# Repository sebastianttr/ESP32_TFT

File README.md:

# ESP32 2.4 inch TFT display driver
A ESP32 TFT board with USB Type C and additional headers for adding sensors.

For any questions make, sure to contact me. You can also DM me at @wired_less_maker
.

# Parts List

This project requires several components: 

* ESP32 WROOM module
  * Preferably a ESP32U or a ESP32S, because of the ability to add an external antenna for better wireless performance
  
* USB Type C Receptable
  * Make sure you select the correct receptable, this is the footprint

* CH340 USB to TTL Converter IC
* LD1117 3V3 Regulator IC
* [OPTIONAL] RFM95 for LoRaWAN
   * If you decide on using LoRaWAN, make sure to also get a U.FL antenna connector 
* 2 SMD Buttons (6 mm X 3.9 mm)
* Passive components
   * 4x 10kOhm 0805 Resistor
   * 2x 5.1kOhm 0805 Resistor 
   * 2x 12kOhm 0805 Resistor
   * 1x Schottky Diode 1206 (the choice is yours)
   * 2x 100nF 0805 Capacitor
   * 1x 10uF 1206 Capacitor
   * 2x 22pF 0603 Capacitor 
   * 1x 12Mhz SMD Crystal 5.0 mm x 3.2 mm
     
     * You will need this configuration. Make sure to look into the datasheet 

   * 2x SOT-23-3 BJT Tranistor of either types: MMBT1000 or MMBT2222
     * S8050 is also OK
* LED
  * For LED, you can use whatever you like.
  * The LED Pin outputs 3.3V from the ESP32, in case you use a LED with a forward voltage lower than ~ 3.3V, you can calculate and add your own resistor at R10
  
# Before usage
  * Before using the device with the TFT touchscreen, make sure to jump these 2 pins above the touchscreen connector: 

  These pins exist to set the brightness of the backlight. In this case, we connect the LED- pin from the touchscreen with 3.3V.

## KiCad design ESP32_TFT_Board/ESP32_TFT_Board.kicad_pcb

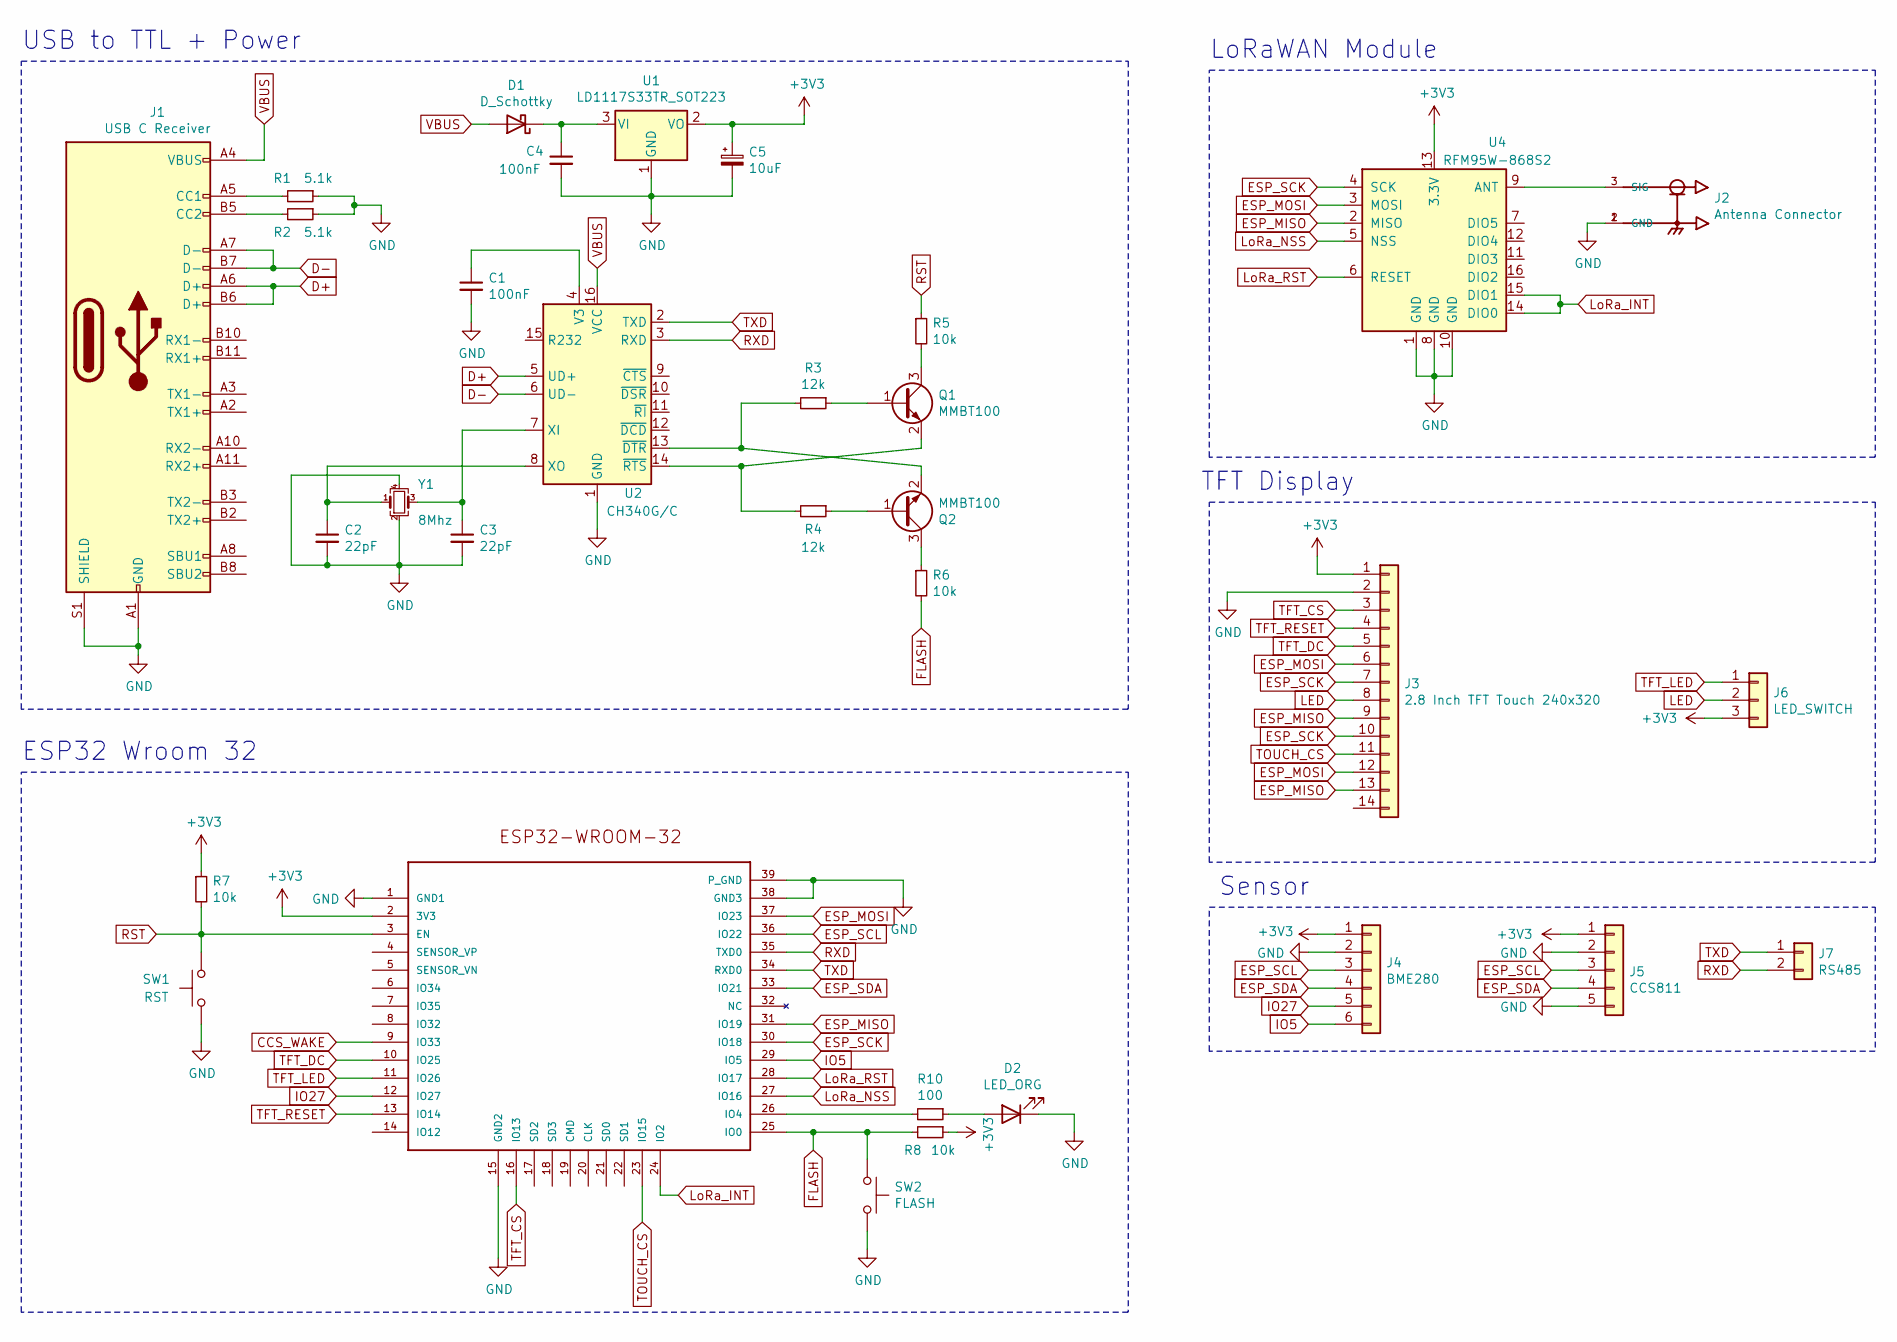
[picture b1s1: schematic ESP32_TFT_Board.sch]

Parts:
C1, C4: 100nF; C_0805_2012Metric_Pad1.15x1.40mm_HandSolder
C2, C3: 22pF; C_0603_1608Metric_Pad1.05x0.95mm_HandSolder
C5: 10uF; C_1206_3216Metric_Pad1.42x1.75mm_HandSolder
D1: D_Schottky; D_1206_3216Metric
D2: LED_ORG; LED_1206_3216Metric_Castellated
J1: USB C Receiver; USB_C_Receptacle_Amphenol_12401548E4-2A
J2: Antenna Connector; HRS_U.FL-R-SMT(01)
J3: 2.8 Inch TFT Touch 240x320; PinHeader_1x14_P2.54mm_Vertical
J4: BME280; PinHeader_1x06_P2.54mm_Vertical
J5: CCS811; PinHeader_1x05_P2.54mm_Vertical
J6: LED_SWITCH; PinHeader_1x03_P1.27mm_Vertical
J7: RS485; PinHeader_1x02_P1.27mm_Vertical
Q1, Q2: MMBT100; SOT-23
R1, R2: 5.1k; R_0805_2012Metric_Pad1.15x1.40mm_HandSolder
R3, R4: 12k; R_0805_2012Metric_Pad1.15x1.40mm_HandSolder
R5, R6, R7, R8: 10k; R_0805_2012Metric_Pad1.15x1.40mm_HandSolder
R10: 100; R_0805_2012Metric_Pad1.15x1.40mm_HandSolder
SW1: RST; SW_SPST_CK_RS282G05A3
SW2: FLASH; SW_SPST_CK_RS282G05A3
U1: LD1117S33TR_SOT223; SOT-223-3_TabPin2
U2: CH340G/C; SOIC-16_3.9x9.9mm_P1.27mm
U3: ESP32-WROOM-32
U4: RFM95W-868S2; Ai-Thinker-Ra-01-LoRa
Y1: 8Mhz; Crystal_SMD_5032-4Pin_5.0x3.2mm

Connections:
+3V3: C5.1, J3.1, J4.1, J5.1, J6.3, R7.1, R8.1, U1.2 (VO), U3.2 (3V3), U4.13 (3.3V)
CCS_WAKE: U3.9 (IO33)
D+: J1.A6 (D+), J1.B6 (D+), U2.5 (UD+)
D-: J1.A7 (D-), J1.B7 (D-), U2.6 (UD-)
ESP_MISO: J3.9, J3.13, U3.31 (IO19), U4.2 (MISO)
ESP_MOSI: J3.6, J3.12, U3.37 (IO23), U4.3 (MOSI)
ESP_SCK: J3.7, J3.10, U3.30 (IO18), U4.4 (SCK)
ESP_SCL: J4.3, J5.3, U3.36 (IO22)
ESP_SDA: J4.4, J5.4, U3.33 (IO21)
FLASH: R6.2, R8.2, SW2.1, U3.25 (IO0)
GND: C1.2, C2.2, C3.2, C4.2, C5.2, D2.1 (K), J1.A1 (GND), J1.A12 (GND), J1.B1 (GND), J1.B12 (GND), J1.S1 (SHIELD), J2.1 (GND), J2.2 (GND), J3.2, J4.2, J5.2, J5.5, R1.1, R2.1, SW1.1, SW2.2, U1.1 (GND), U2.1 (GND), U3.1 (GND1), U3.15 (GND2), U3.38 (GND3), U3.39 (P_GND), U4.1 (GND), U4.8 (GND), U4.10 (GND), Y1.2, Y1.4
IO5: J4.6, U3.29 (IO5)
IO27: J4.5, U3.12 (IO27)
LED: J3.8, J6.2
LoRa_INT: U3.24 (IO2), U4.14 (DIO0), U4.15 (DIO1)
LoRa_NSS: U3.27 (IO16), U4.5 (NSS)
LoRa_RST: U3.28 (IO17), U4.6 (RESET)
unnamed: C1.1, U2.4 (V3)
unnamed: C2.1, U2.8 (XO), Y1.1
unnamed: C3.1, U2.7 (XI), Y1.3
unnamed: C4.1, D1.1 (K), U1.3 (VI)
unnamed: D2.2 (A), R10.1
unnamed: J1.A5 (CC1), R1.2
unnamed: J1.B5 (CC2), R2.2
unnamed: J2.3 (SIG), U4.9 (ANT)
unnamed: Q1.1 (B), R3.1
unnamed: Q1.2 (E), R4.2, U2.14 (~RTS)
unnamed: Q1.3 (C), R5.2
unnamed: Q2.1 (B), R4.1
unnamed: Q2.2 (E), R3.2, U2.13 (~DTR)
unnamed: Q2.3 (C), R6.1
unnamed: R10.2, U3.26 (IO4)
RST: R5.1, R7.2, SW1.2, U3.3 (EN)
RXD: J7.2, U2.3 (RXD), U3.35 (TXD0)
TFT_CS: J3.3, U3.16 (IO13)
TFT_DC: J3.5, U3.10 (IO25)
TFT_LED: J6.1, U3.11 (IO26)
TFT_RESET: J3.4, U3.13 (IO14)
TOUCH_CS: J3.11, U3.23 (IO15)
TXD: J7.1, U2.2 (TXD), U3.34 (RXD0)
VBUS: D1.2 (A), J1.A4 (VBUS), J1.A9 (VBUS), J1.B4 (VBUS), J1.B9 (VBUS), U2.16 (VCC)

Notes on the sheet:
USB to TTL + Power
ESP32 Wroom 32
LoRaWAN Module
TFT Display
Sensor

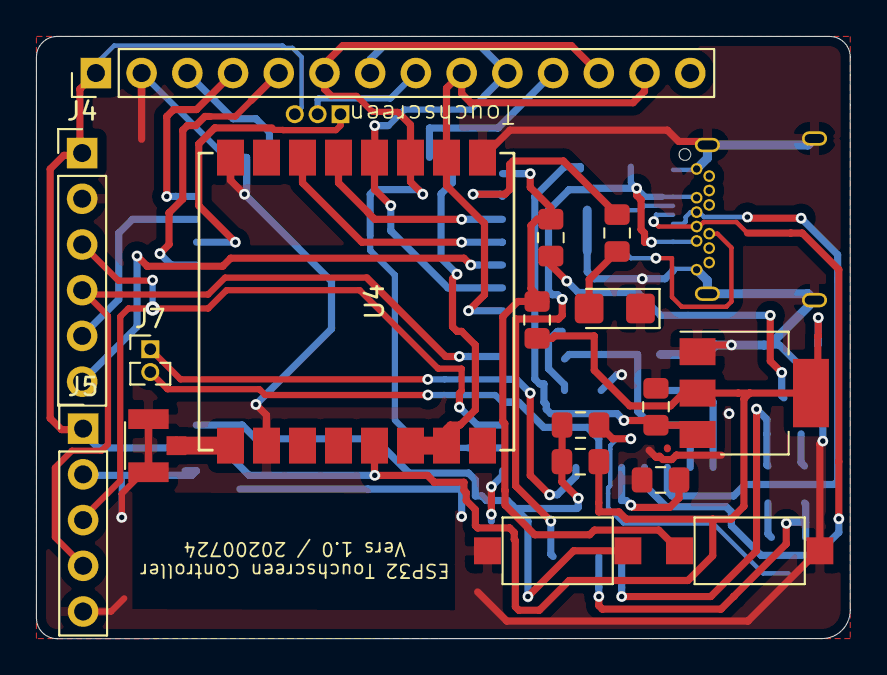
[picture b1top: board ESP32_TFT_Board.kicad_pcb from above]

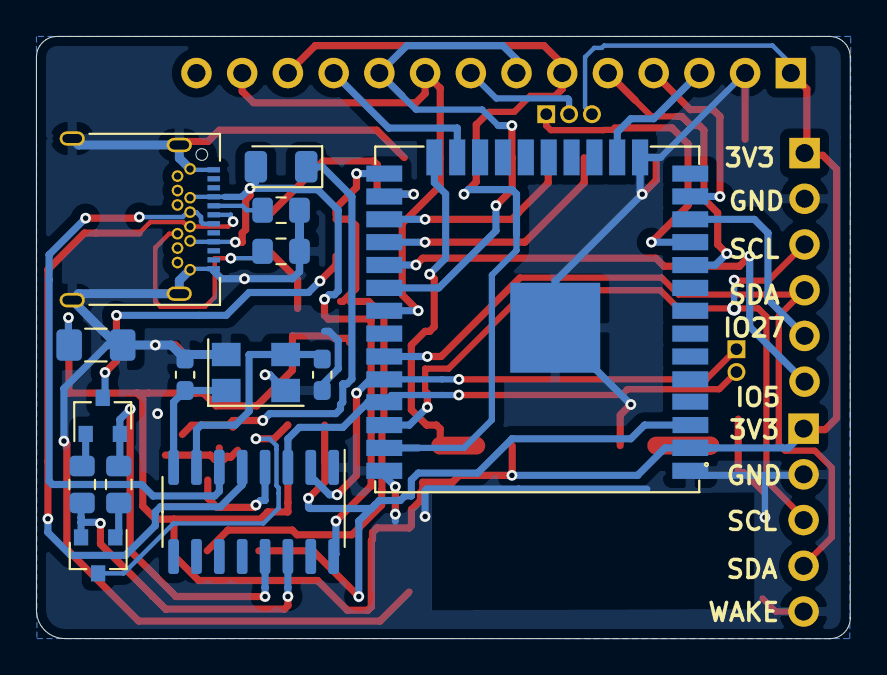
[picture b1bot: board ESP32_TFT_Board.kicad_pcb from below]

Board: 2 copper layers, 45.2 x 33.5 mm, 32 parts (14 on the bottom side), 40 nets.

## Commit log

2020-08-27 Changes to be committed: new file: ESP32_TFT_Board/ESP32_TFT_Board-NPTH.drl new file: ESP32_TFT_Board/ESP32_TFT_Board-PTH.drl new file: ESP32_TFT_Board/ESP32_TFT_Board-cache.lib new file: ESP32_TFT_B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
